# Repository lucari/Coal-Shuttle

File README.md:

# Coal-Shuttle

This is an Arduino based train shuttle controller for a model railway coal-hopper.

The direcrtion of the train is controlled by the on-off-on switch connected to the resistor divider on the Analog3 pin. The trimmers connected to the other Analog pins are used to control the Delay and Dwell for when the train is stopped. A Reed Switch is used to determine when a Coal Truck is in position under the shute. In forward mode, this will stop the train and turn on the converyor belt. It wil then wait for the bucket tip mercury switch to trigger, showing the coal has been delivered. After a period of time, the track power is enabled to move to the next truck.

The direction switch also controls the direction of two points that will send the train either through the Coal Loading chute path, or through the Coal Unloading path.

The pin assignment is:

  D2  - Track Power  
  D3  - Track Direction  
  D4  - Reed Switch (Train Detect)  
  D5  - Tilt Switch (Coal Tipper)  
  D6  - Conveyor Power  
  D7  - Spare  
  D8  - Points 1 Normal (Relay 1)  
  D9  - Points 1 Divert (Relay 2)  
  D10 - Points 2 Normal (Relay 3)  
  D11 - Points 2 Divert (Relay 4)  
  D12 - Red LED  
  D13 - Green LED  

  A0 - Train Detect Delay  
  A1 - Coal Tipper Dwell  
  A2 - Spare  
  A3 - Direction (0v - 2.5v - 5v)  
  
_It should be noted that there is a small design flaw on V1 of the board. The Relay module interface uses 5v from the external regulator. This should be from the Arduino 5v so it is common with the output pins. This is so it can drive the opto-coupler LED correctly (common 5v not ground). However, the external regulator 5v <ins>must</ins> be used to drive the relays (also known as JD Power). These draw too much current through the Arduino regulator. Ideally, the 5v lines should be through a jumper so the correct one can be selected for the interface type. This will be fixed on the next board. In the short term, the 5v from the I2C connector can be used for the relay 'IN' connections and the 5v on the module interface can be used for JD power._

## Arduino Code
The code is held under the Arduino folder. 

## Kicad Files
A Custom PCB was made for this and can be found under the Kicad folder.

## Completed Boards
The image below shows a completed board.

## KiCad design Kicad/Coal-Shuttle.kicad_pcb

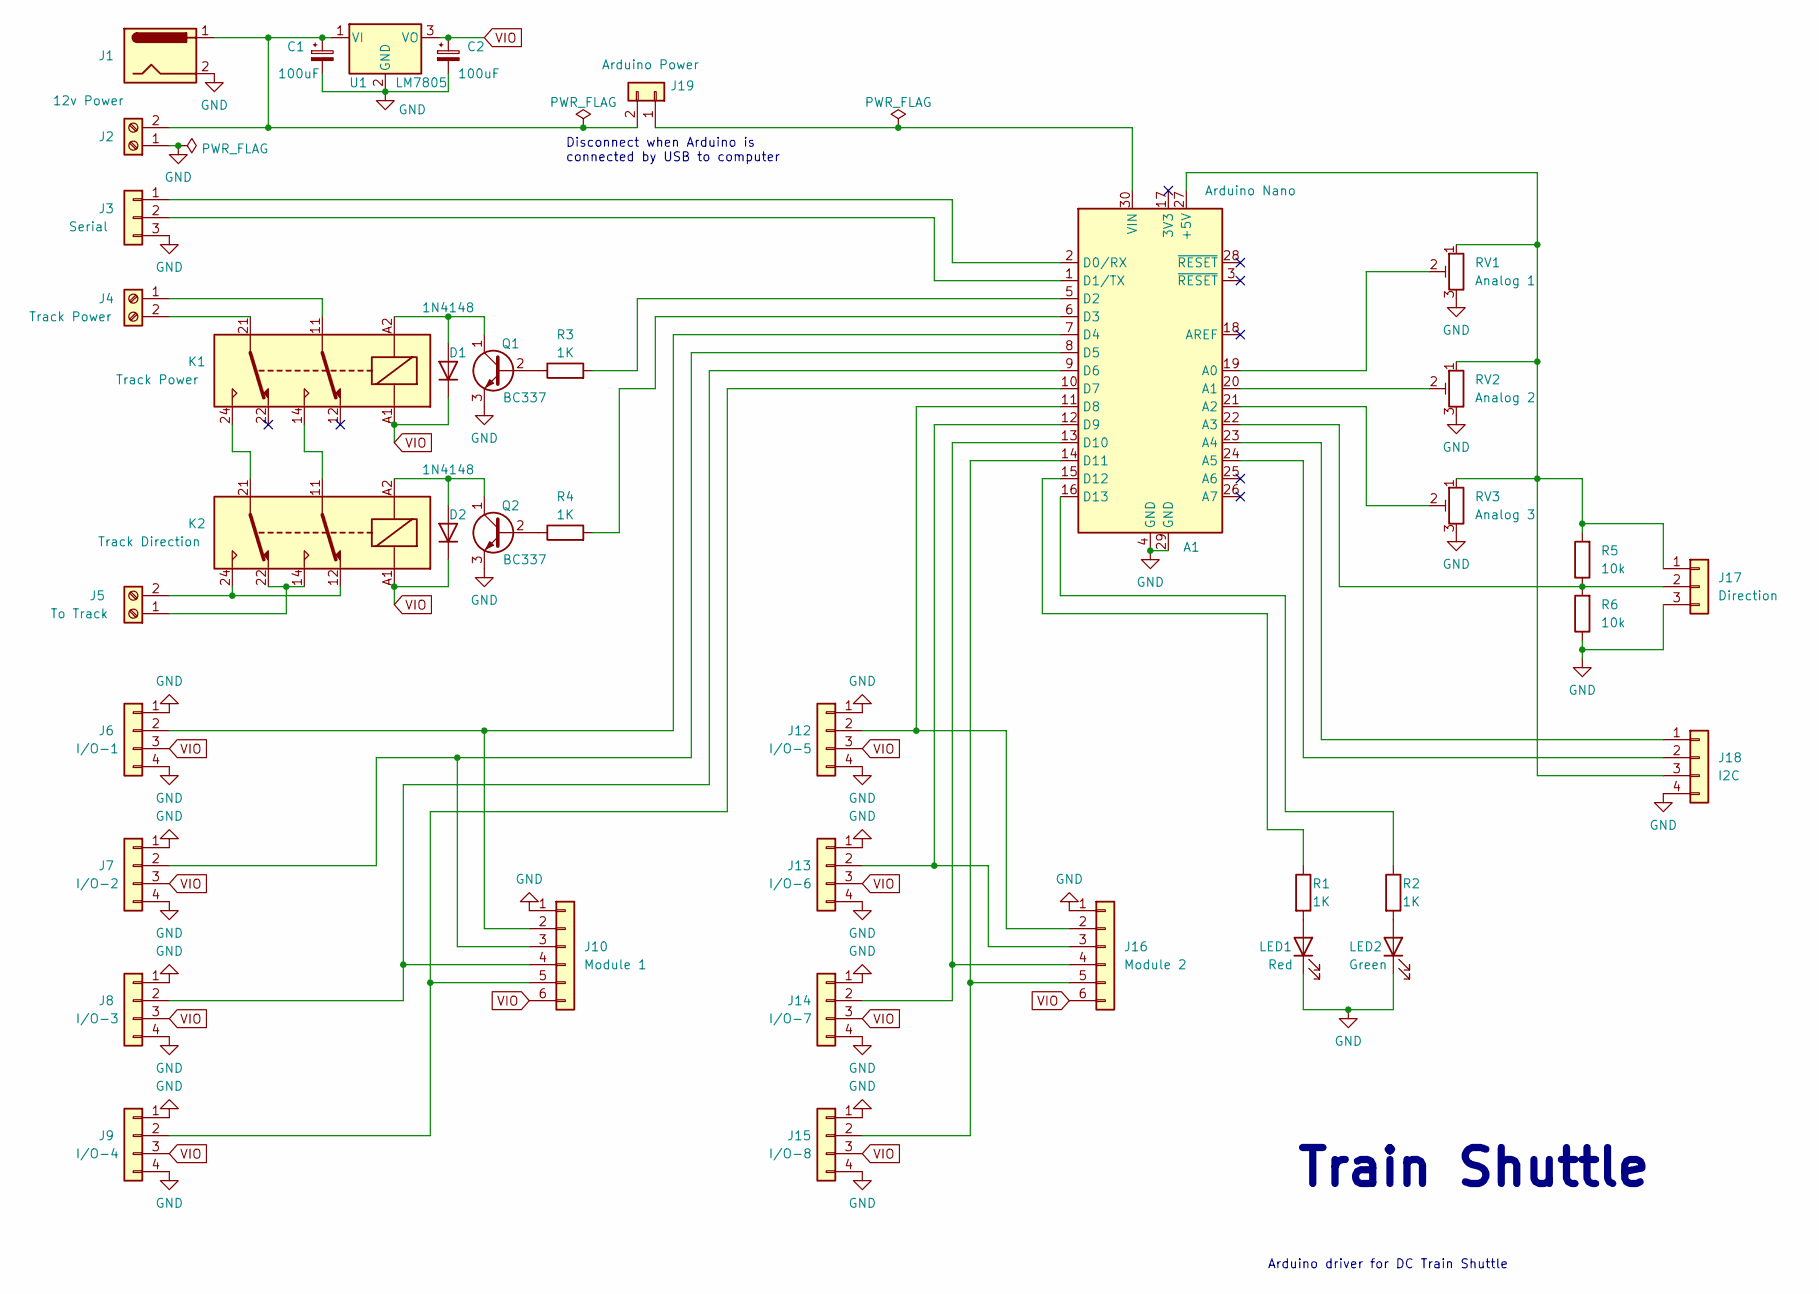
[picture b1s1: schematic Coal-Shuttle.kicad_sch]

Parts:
A1: Arduino Nano; Arduino_Nano
C1, C2: 100uF; CP_Radial_D7.5mm_P2.50mm
D1, D2: 1N4148; D_DO-35_SOD27_P7.62mm_Horizontal
J1: 12v Power; BarrelJack_Horizontal
J2: 12v Power; TerminalBlock_Phoenix_MKDS-1,5-2-5.08_1x02_P5.08mm_Horizont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
J3: Serial; PinHeader_1x03_P2.54mm_Vertical
J4: Track Power; TerminalBlock_Phoenix_MKDS-1,5-2-5.08_1x02_P5.08mm_Horizont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
J5: To Track; TerminalBlock_Phoenix_MKDS-1,5-2-5.08_1x02_P5.08mm_Horizont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
J6: I/O-1; PinHeader_1x04_P2.54mm_Vertical
J7: I/O-2; PinHeader_1x04_P2.54mm_Vertical
J8: I/O-3; PinHeader_1x04_P2.54mm_Vertical
J9: I/O-4; PinHeader_1x04_P2.54mm_Vertical
J10: Module 1; PinHeader_1x06_P2.54mm_Vertical
J12: I/O-5; PinHeader_1x04_P2.54mm_Vertical
J13: I/O-6; PinHeader_1x04_P2.54mm_Vertical
J14: I/O-7; PinHeader_1x04_P2.54mm_Vertical
J15: I/O-8; PinHeader_1x04_P2.54mm_Vertical
J16: Module 2; PinHeader_1x06_P2.54mm_Vertical
J17: Direction; PinHeader_1x03_P2.54mm_Vertical
J18: I2C; PinHeader_1x04_P2.54mm_Vertical
J19: Arduino Power; PinHeader_1x02_P2.54mm_Vertical
K1: Track Power; Relay_DPDT_Finder_30.22
K2: Track Direction; Relay_DPDT_Finder_30.22
LED1: Red; LED_D5.0mm
LED2: Green; LED_D5.0mm
Q1, Q2: BC337; TO-92_Inline_Wide
R1, R2, R3, R4: 1K; R_Axial_DIN0207_L6.3mm_D2.5mm_P7.62mm_Horizontal
R5, R6: 10k; R_Axial_DIN0207_L6.3mm_D2.5mm_P7.62mm_Horizontal
RV1: Analog 1; Trimpot_and_Pins
RV2: Analog 2; Trimpot_and_Pins
RV3: Analog 3; Trimpot_and_Pins
U1: LM7805; TO-220-3_Vertical

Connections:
GND: A1.4 (GND), A1.29 (GND), C1.2, C2.2, J1.2, J1.3, J2.1, J3.3, J6.1, J6.4, J7.1, J7.4, J8.1, J8.4, J9.1, J9.4, J10.1, J12.1, J12.4, J13.1, J13.4, J14.1, J14.4, J15.1, J15.4, J16.1, J17.3, J18.4, LED1.1 (K), LED2.1 (K), Q1.3 (E), Q2.3 (E), R6.1, RV1.3, RV2.3, RV3.3, U1.2 (GND); also elsewhere on the board
unnamed 1: A1.1 (D1/TX), J3.2; also elsewhere on the board
unnamed 2: A1.2 (D0/RX), J3.1; also elsewhere on the board
unnamed 3: A1.5 (D2), R3.2; also elsewhere on the board
unnamed 4: A1.6 (D3), R4.2; also elsewhere on the board
unnamed 5: A1.7 (D4), J6.2, J10.2; also elsewhere on the board
unnamed 6: A1.8 (D5), J7.2, J10.3; also elsewhere on the board
unnamed 7: A1.9 (D6), J8.2, J10.4; also elsewhere on the board
unnamed 8: A1.10 (D7), J9.2, J10.5; also elsewhere on the board
unnamed 9: A1.11 (D8), J12.2, J16.2; also elsewhere on the board
unnamed 10: A1.12 (D9), J13.2, J16.3; also elsewhere on the board
unnamed 11: A1.13 (D10), J14.2, J16.4; also elsewhere on the board
unnamed 12: A1.14 (D11), J15.2, J16.5; also elsewhere on the board
unnamed 13: A1.15 (D12), R1.1; also elsewhere on the board
unnamed 14: A1.16 (D13), R2.1; also elsewhere on the board
unnamed 15: A1.19 (A0), RV1.2; also elsewhere on the board
unnamed 16: A1.20 (A1), RV2.2; also elsewhere on the board
unnamed 17: A1.21 (A2), RV3.2; also elsewhere on the board
unnamed 18: A1.22 (A3), J17.2, R5.1, R6.2; also elsewhere on the board
unnamed 19: A1.23 (A4), J18.1; also elsewhere on the board
unnamed 20: A1.24 (A5), J18.2; also elsewhere on the board
unnamed 21: A1.27 (+5V), J17.1, J18.3, R5.2, RV1.1, RV2.1, RV3.1; also elsewhere on the board
unnamed 22: A1.30 (VIN), J19.1; also elsewhere on the board
unnamed: C1.1, J1.1, J2.2, J19.2, U1.1 (VI)
unnamed: D1.2 (A), K1.A2, Q1.1 (C)
unnamed: D2.2 (A), K2.A2, Q2.1 (C)
unnamed: J4.1, K1.11
unnamed: J4.2, K1.21
unnamed: J5.1, K2.14, K2.22
unnamed: J5.2, K2.12, K2.24
unnamed: K1.14, K2.11
unnamed: K1.24, K2.21
unnamed: LED1.2 (A), R1.2
unnamed: LED2.2 (A), R2.2
unnamed: Q1.2 (B), R3.1
unnamed: Q2.2 (B), R4.1
VIO: C2.1, D1.1 (K), D2.1 (K), J6.3, J7.3, J8.3, J9.3, J10.6, J12.3, J13.3, J14.3, J15.3, J16.6, K1.A1, K2.A1, U1.3 (VO)

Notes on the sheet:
Arduino driver for DC Train Shuttle
Disconnect when Arduino is connected by USB to computer
Train Shuttle

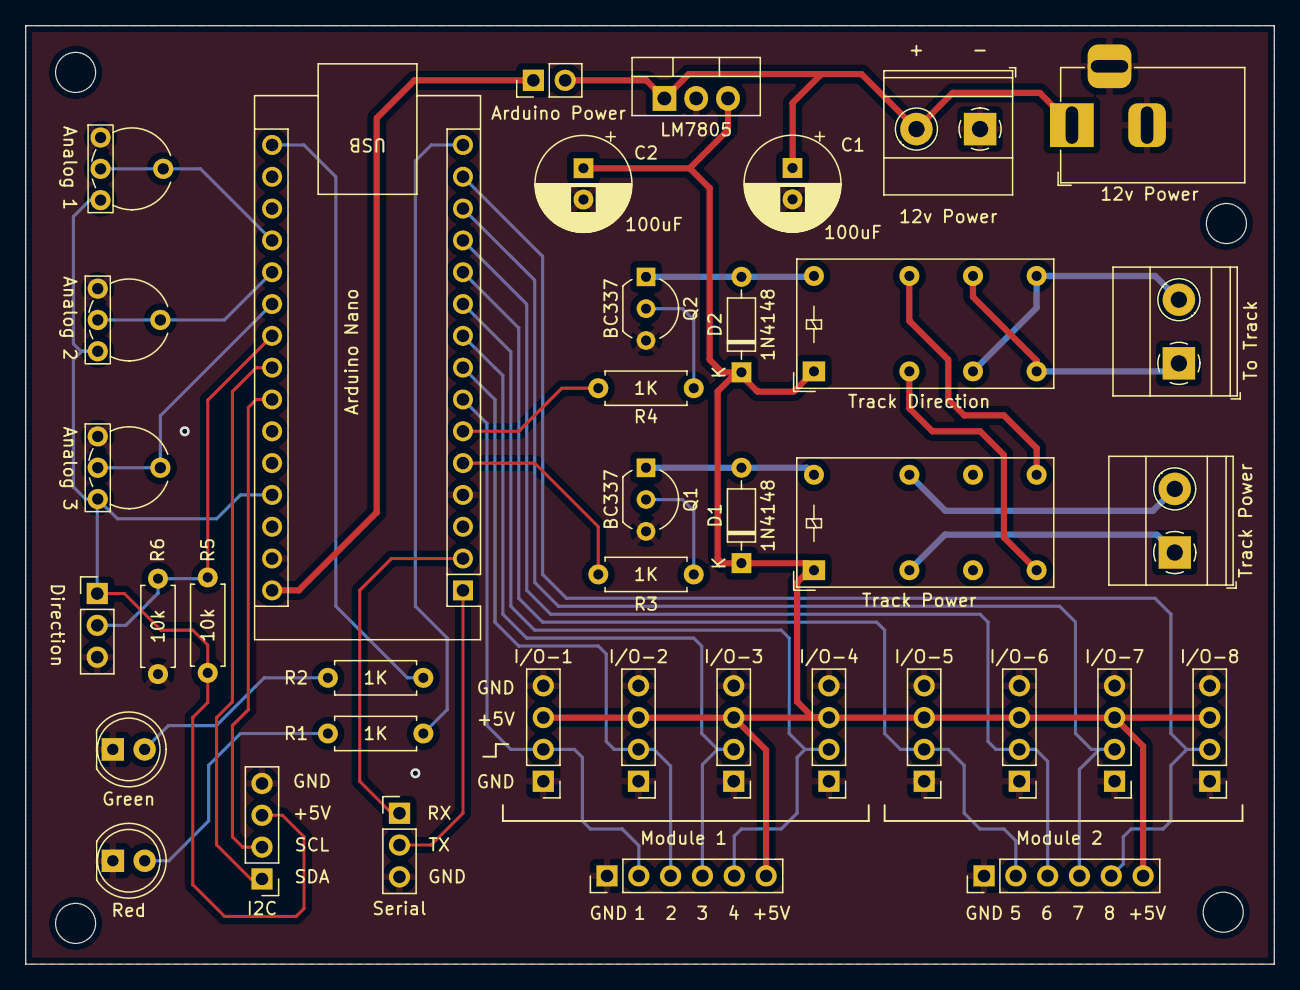
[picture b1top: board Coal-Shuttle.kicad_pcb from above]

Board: 2 copper layers, 99.7 x 74.9 mm, 39 parts (0 on the bottom side), 37 nets.

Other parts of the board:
locked: Arduino Nano; Arduino_Nano

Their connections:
GND: locked.4 (GND), locked.29 (GND); also elsewhere on the board
unnamed 1: locked.1 (D1/TX); also elsewhere on the board
unnamed 2: locked.2 (D0/RX); also elsewhere on the board
unnamed 3: locked.5 (D2); also elsewhere on the board
unnamed 4: locked.6 (D3); also elsewhere on the board
unnamed 5: locked.7 (D4); also elsewhere on the board
unnamed 6: locked.8 (D5); also elsewhere on the board
unnamed 7: locked.9 (D6); also elsewhere on the board
unnamed 8: locked.10 (D7); also elsewhere on the board
unnamed 9: locked.11 (D8); also elsewhere on the board
unnamed 10: locked.12 (D9); also elsewhere on the board
unnamed 11: locked.13 (D10); also elsewhere on the board
unnamed 12: locked.14 (D11); also elsewhere on the board
unnamed 13: locked.15 (D12); also elsewhere on the board
unnamed 14: locked.16 (D13); also elsewhere on the board
unnamed 15: locked.19 (A0); also elsewhere on the board
unnamed 16: locked.20 (A1); also elsewhere on the board
unnamed 17: locked.21 (A2); also elsewhere on the board
unnamed 18: locked.22 (A3); also elsewhere on the board
unnamed 19: locked.23 (A4); also elsewhere on the board
unnamed 20: locked.24 (A5); also elsewhere on the board
unnamed 21: locked.27 (+5V); also elsewhere on the board
unnamed 22: locked.30 (VIN); also elsewhere on the board
